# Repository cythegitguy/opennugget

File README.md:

# Excuse the spaghetti
This repo is currently an absolute mess and I'm trying to move everything online so collaboration is easier. Updated CAD and EasyEDA drawings (currently being ported from KiCad) will be available soon.

# What is this project?
There have been a lot of fantastic and open-source DAP designs popping up recently, but nothing that has quite scratched my itch for a more modern and capable iPod-style DAP. While [tangara](https://www.crowdsupply.com/cool-tech-zone/tangara) and the [Echo R1](https://github.com/amachronic/echoplayer) both look like fantastic devices, they don't quite meet my wants from a modern DAP. 
To me, the platonic ideal for a DAP is the iPod Video. Unfortunately, despite having spent tons of time and money dealing with iPods, they aren't always reliable, and fixing them can be really expensive. 
This project aims to recreate the iPod Video experience in a modern chassis with improved and repairable hardware, native RockBox support and comprehensive documentation for anyone looking to repair or contribute.

# What are those requirements?

- RockBox: The fantastic people of [RockBox](https://www.rockbox.org/) made the arguably best firmware for most music players. Starting from scratch with a documented system and common MCU should be boons to any developers

- OLED: While the focus of a DAP is music, a nice screen is always a plus. OLED offers much higher brightness compared to LCD displays and reduced power draw if using a dark UI. This used to be unfeasible, but new 2.7" OLED panels can be had for ~$80 US and bulk orders greatly reduce that price

- MicroSD: This isn't an innovation, but some new DAPs seem to ignore the standard

- Easily swappable batteries: LiPo cells have great energy density and are cheap to replace. Making batteries easily swappable just improves the end-user experience

- Click wheel interface: Almost no other DAP I've found has a satisfying click wheel interface. The inniosasis Y1 is bearable but doesn't have upgradable storage and the HiFi walker H2 has a jog wheel with separate buttons

- Bluetooth: Yes RockBox devs I hear you, bluetooth will never be supported etc. etc. That isn't in rockbox's scope, I just want to provide support for it through the hardware and an integrated antenna.

- Customisability: Being able to customize things you own is great, and this player was designed with customization in mind. The faceplate, wheel covering, center button and outer housing are all easily replacable and designed to be SLA 3D printed with minimal cost, either by you or a third-party service. The outer shell was designed with sheet metal forming in place and can be made on a press brake.

- Repair: Working in a small space makes the size constraints for this player really tough, so repairability isn't as good as some larger products. In the current edition, the 3.5mm jack and HOLD switch are on a separate daugterboard and designed to be easily replaced (the 3.5mm jack can also be replaced with a 2.5mm or 4.4mm Balanced jack). As mentioned above, the battery and microSD are both also easy to replace and an intelligent BMS using the TP4056 is used to prevent battery damage.

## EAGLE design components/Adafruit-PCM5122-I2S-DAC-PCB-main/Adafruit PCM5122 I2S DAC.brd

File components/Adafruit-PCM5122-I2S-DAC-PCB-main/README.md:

## Adafruit PCM5122 I2S DAC with Line Level Output - HW, I2C or SPI PCB

<a href="http://www.adafruit.com/products/6421"><br/>
Click here to purchase one from the Adafruit shop</a>

PCB files for the Adafruit PCM5122 I2S DAC with Line Level Output - HW, I2C or SPI. 

Format is EagleCAD schematic and board layout
* https://www.adafruit.com/product/6421

### Description

For converting digital I2S audio from your ESP32/RP2350 or Raspberry Pi, you'll need a digital-to-analog-converter (DAC). And the <b>Adafruit PCM5122 I2S DAC</b> is both powerful and easy to use - with excellent audio quality!  It's got clean, high-quality, stereo audio and does not need any MCLK signal, or I2C configuration. Literally just pipe some I2S audio in and it ill just work.

The default hardware mode is excellent for quick starts, and, for those who do want configurability such as volume control / software mute / EQ / filters, it's also easy to set up the chip for I2C or SPI interfacing with the two MODE pins.

The PCM5122 has excellent audio specs, with 112dB signal-to-noise/dynamic range, and -93 dB THD.

This breakout makes I2S digital audio easy: all you need to do is power it with 3~5VDC, and provide BCLK (bit clock), WSEL (left/right word select), and DIN (data in). The data lines are 3.3V logic only. By default it's configured for I2S but you can also do Left-Justified by toggling the Format pin. Audio can be 16, 24 or 32-bit wide, the chip will automagically determine the right format from the WSEL / BCLK ratio. No MCLK pin is needed, the chip will auto-generate it internally from the bit clock - or you can provide it on the MCLK input if you want.

For hardware (not I2C/SPI config mode) the other breakout pads provide:

* <b>Filtering</b> (change from normal to low-latency by pulling high)
* <b>De-emphasis</b>
* <b>Mute</b> (pull low to quickly set the outputs to ground), and de-emphasis for 44.1khz audio (default is off)
* Three <b>ATTenuation/gain</b> pins that can be used for changing the gain from -6dB to +15dB. See the datasheet's Table 3 for the pin-to-gain settings.

For I2C/SPI configuration mode, gain/volume, filtering and de-emphasis is done over digital register commands. The hardware Mute pin still works as expected.

The audio outputs are also available on breakout pads if you want to wire directly without using the 3.5mm jack. Audio output is not AC-coupled because it is centered on ground: you can plug it into anything that is either AC coupled or has the same ground reference. Note that this is a line-level output, it cannot drive headphones - the output is for no less than 1K ohm loads!

Each order comes with one I2S Stereo DAC breakout and some header you can solder on for breadboard usage.

### License

Adafruit invests time and resources providing this open source design, please support Adafruit and open-source hardware by purchasing products from [Adafruit](https://www.adafruit.com)!

Designed by Limor Fried/Ladyada for Adafruit Industries.

Creative Commons Attribution/Share-Alike, all text above must be included in any redistribution. 
See license.txt for additional details.

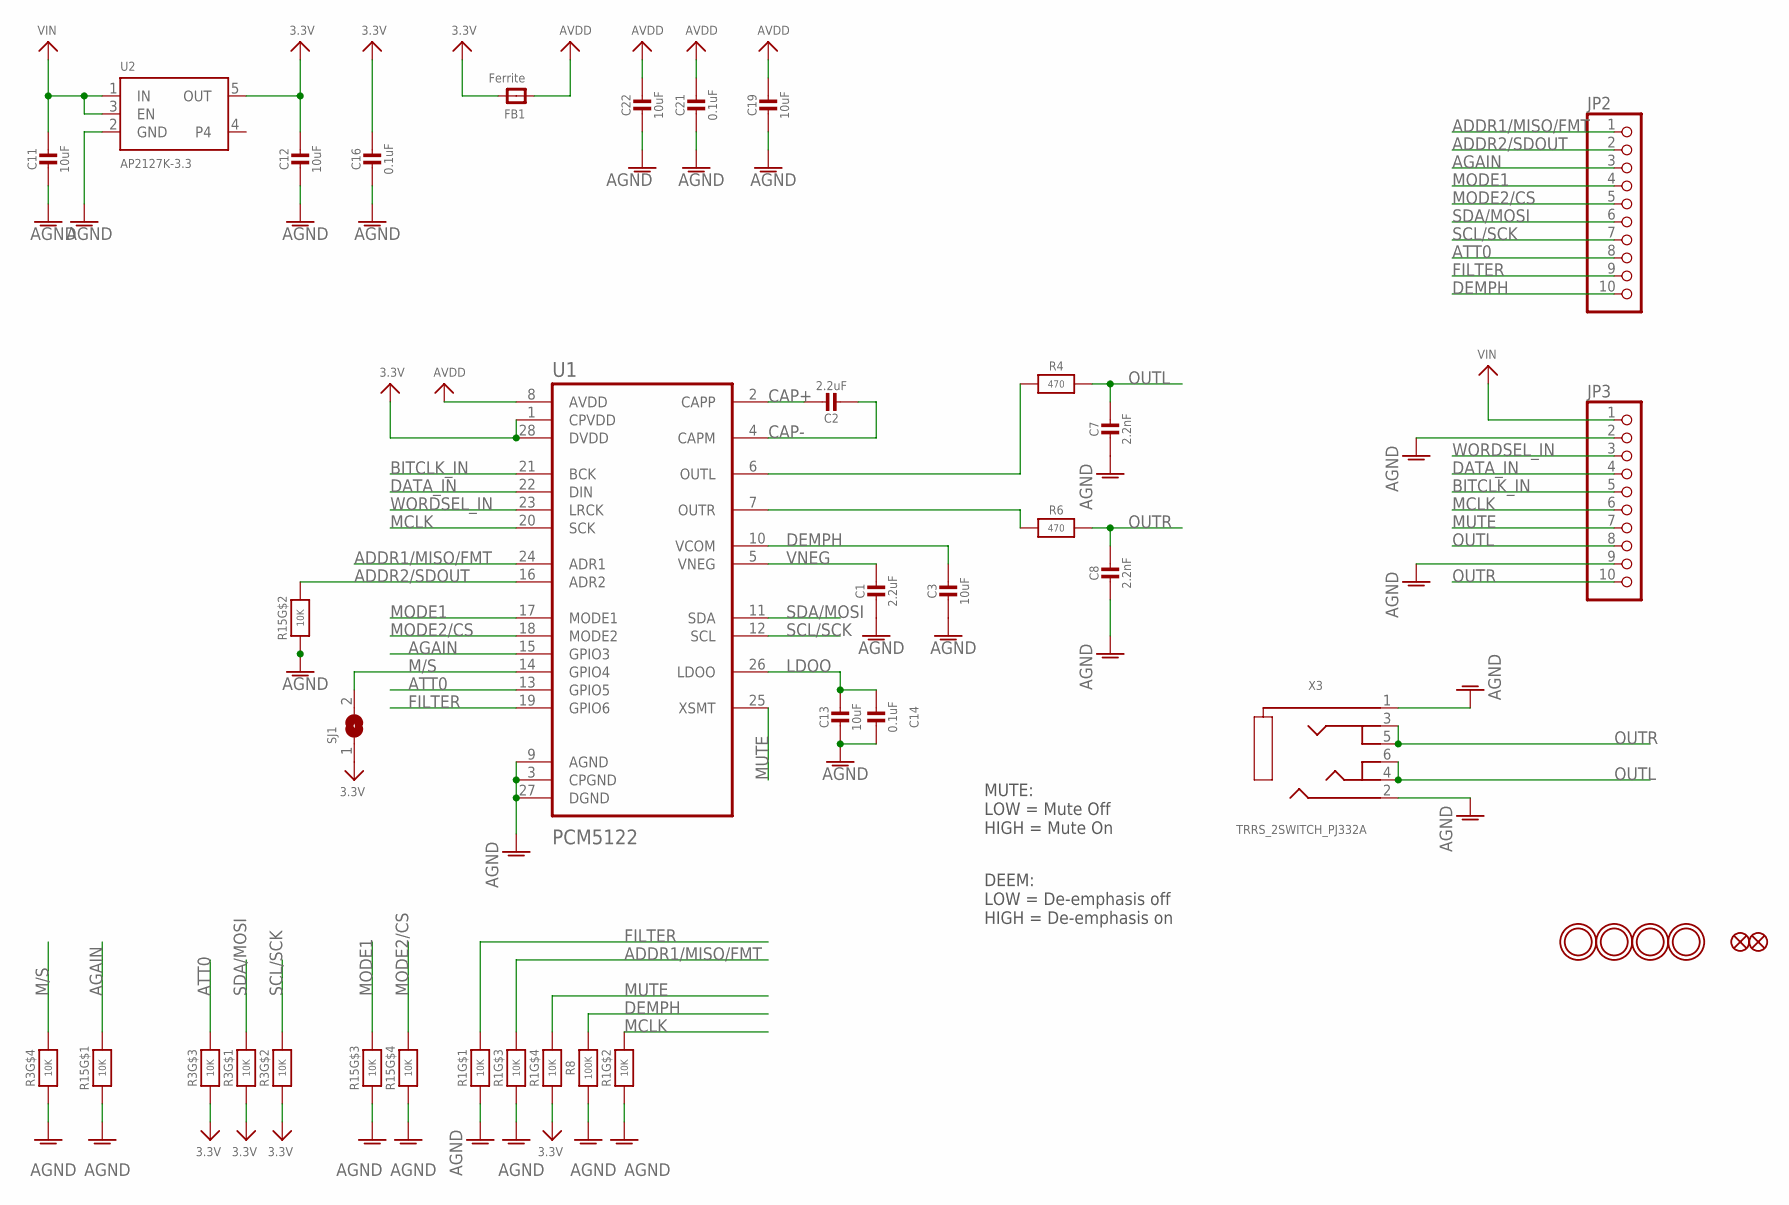
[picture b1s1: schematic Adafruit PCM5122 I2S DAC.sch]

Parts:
C1, C2: 2.2uF; 0603-NO
C3, C11, C12, C13, C19, C22: 10uF; 0805-NO
C7, C8: 2.2nF; 0603-NO
C14, C16, C21: 0.1uF; 0603-NO
FB1: Ferrite; 0603-NO
FID1, FID2: FIDUCIAL_0.5MM
JP2, JP3: HEADER-1X1070MIL; 1X10_ROUND70
R1, R3, R15: 10K; RESPACK_4X0603
R4, R6: 470; 0603-NO
R8: 100K; 0603-NO
SJ1: SOLDERJUMPER; SOLDERJUMPER_ARROW_NOPASTE
U1: PCM5122; SSOP-28N
U2: AP2127K-3.3; SOT23-5
U$11, U$12, U$13, U$14: MOUNTINGHOLE2.5; MOUNTINGHOLE_2.5_PLATED
X3: TRRS_2SWITCH_PJ332A; PJ-332A

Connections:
3.3V: C12.1, C16.1, FB1.2, R1.4 (1), R3.1, R3.2 (1), R3.3 (1), SJ1.1, U1.1 (CPVDD), U1.28 (DVDD), U2.5 (OUT)
ADDR1/MISO/FMT: JP2.1, R1.6 (2), U1.24 (ADR1)
ADDR2/SDOUT: JP2.2, R15.7 (2), U1.16 (ADR2)
AGAIN: JP2.3, R15.8 (2), U1.15 (GPIO3)
AGND: C1.2, C3.2, C7.2, C8.2, C11.2, C12.2, C13.2, C14.2, C16.2, C19.2, C21.2, C22.2, JP3.2, JP3.9, R1.1, R1.2 (1), R1.3 (1), R3.4 (1), R8.1, R15.1, R15.2 (1), R15.3 (1), R15.4 (1), U1.3 (CPGND), U1.9 (AGND), U1.27 (DGND), U2.2 (GND), X3.1 (RING), X3.2 (RING1)
ATT0: JP2.8, R3.6 (2), U1.13 (GPIO5)
AVDD: C19.1, C21.1, C22.1, FB1.1, U1.8 (AVDD)
BITCLK_IN: JP3.5, U1.21 (BCK)
CAP+: C2.1, U1.2 (CAPP)
CAP-: C2.2, U1.4 (CAPM)
DATA_IN: JP3.4, U1.22 (DIN)
DEMPH: C3.1, JP2.10, R8.2, U1.10 (VCOM)
FILTER: JP2.9, R1.8 (2), U1.19 (GPIO6)
LDOO: C13.1, C14.1, U1.26 (LDOO)
M/S: R3.5 (2), SJ1.2, U1.14 (GPIO4)
MCLK: JP3.6, R1.7 (2), U1.20 (SCK)
MODE1: JP2.4, R15.6 (2), U1.17 (MODE1)
MODE2/CS: JP2.5, R15.5 (2), U1.18 (MODE2)
MUTE: JP3.7, R1.5 (2), U1.25 (XSMT)
unnamed: R6.1, U1.7 (OUTR)
unnamed: R4.1, U1.6 (OUTL)
OUTL: C7.1, JP3.8, R4.2, X3.4 (TIP), X3.6 (TIP_SW)
OUTR: C8.1, JP3.10, R6.2, X3.3 (RING2), X3.5 (R2_SW)
SCL/SCK: JP2.7, R3.7 (2), U1.12 (SCL)
SDA/MOSI: JP2.6, R3.8 (2), U1.11 (SDA)
VIN: C11.1, JP3.1, U2.1 (IN), U2.3 (EN)
VNEG: C1.1, U1.5 (VNEG)
WORDSEL_IN: JP3.3, U1.23 (LRCK)

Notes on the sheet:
MUTE: LOW = Mute Off HIGH = Mute On
DEEM: LOW = De-emphasis off HIGH = De-emphasis on

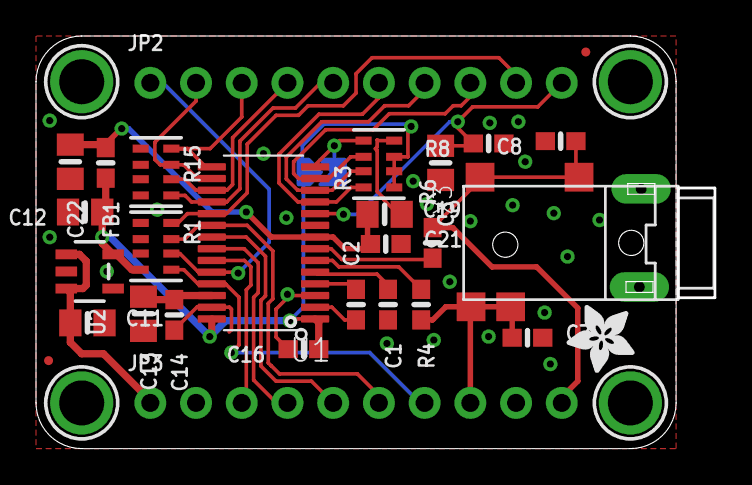
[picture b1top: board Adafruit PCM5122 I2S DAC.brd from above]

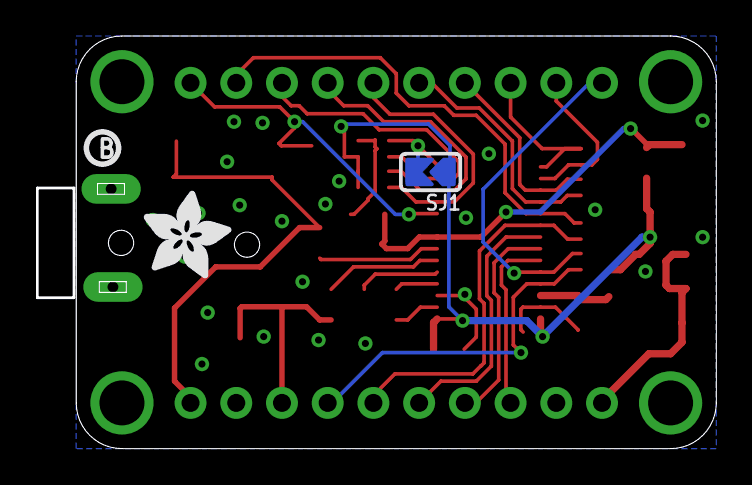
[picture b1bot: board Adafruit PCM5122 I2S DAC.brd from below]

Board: 2 copper layers, 37.6 x 22.8 mm, 61 parts (6 on the bottom side), 28 nets.

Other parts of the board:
PLABEL0: PLABEL0
PLABEL1: PLABEL1
PLABEL2: PLABEL2
PLABEL3, PLABEL4: PLABEL4
PLABEL5: PLABEL5
PLABEL6: PLABEL6
PLABEL7: PLABEL7
PLABEL8: PLABEL8
PLABEL9: PLABEL9
PLABEL10: PLABEL10
PLABEL11: PLABEL11
PLABEL12: PLABEL12
PLABEL13: PLABEL13
PLABEL14: PLABEL14
PLABEL15: PLABEL15
PLABEL16: PLABEL16
PLABEL17: PLABEL17
PLABEL18: PLABEL18
PLABEL19: PLABEL19
PLABEL20: PLABEL20
PLABEL21: PLABEL21
PLABEL22: PLABEL22
PLABEL23: PLABEL23
PLABEL24: PLABEL24
PLABEL25: PLABEL25
U$5: PCBFEAT-REV-040
U$6: ADAFRUIT_5MM
U$29: ADAFRUIT_3.5MM

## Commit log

2026-04-15 Updated kiCad libs
2026-04-25 Updated files (need to organize)
2026-04-25 removed important info
2026-04-25 asdf
2026-04-25 Updated again due to OCD

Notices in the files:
parts and their libraries:
microbuilder: This work is placed in the public domain, and may be freely used for commercial and non-commercial work with the following conditions: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
